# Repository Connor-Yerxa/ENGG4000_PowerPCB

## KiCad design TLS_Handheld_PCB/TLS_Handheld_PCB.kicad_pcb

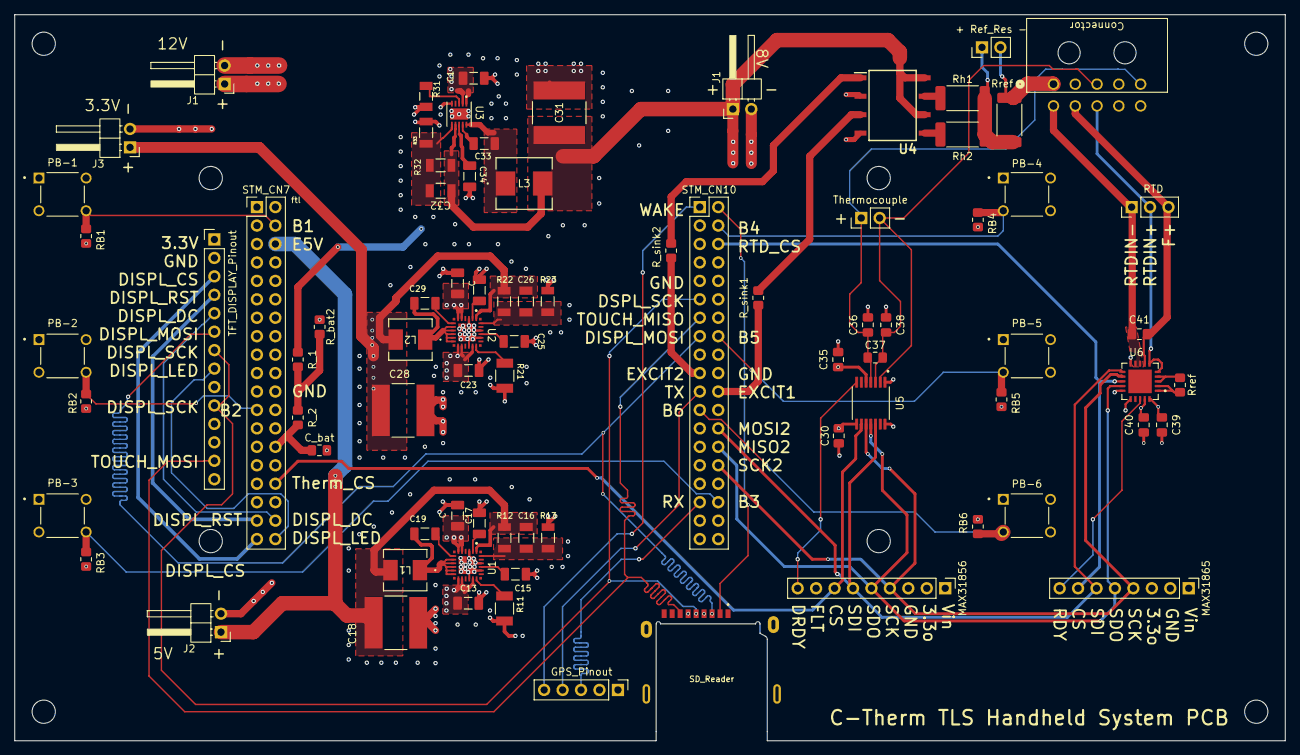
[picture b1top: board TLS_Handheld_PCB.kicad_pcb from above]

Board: 4 copper layers, 175.0 x 100.0 mm, 86 parts (0 on the bottom side), 63 nets.

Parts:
+ Ref_Res -: PinHeader_1x02_P2.54mm_Vertical
C, C13, C17, C23, C27, C34: 1uF; CAPC3216X180N
C1: 4.7uF; CAPC3216X180N
C15, C25: 1nF; CAPC3216X100N
C16, C26, C32: 10pF; CAP_C1206C-X7R-EB_KEM
C18, C28, C31: 100uF; CAP_NTJ_76B_9.5T_NIP
C19, C29, C33: 0.1uF; CAPC3216X100N
C30, C35, C37: 0.1uF; C_0805_2012Metric_Pad1.18x1.45mm_HandSolder
C36, C38, C39, C40, C41: 0.01uF; C_0805_2012Metric_Pad1.18x1.45mm_HandSolder
C#2: 1uF; CAPC3216X180N
C_bat: 0.1uF; C_0805_2012Metric_Pad1.18x1.45mm_HandSolder
Connector: 0430451000
GPS_Pinout: PinHeader_1x05_P2.54mm_Vertical
J1, J1#2, J2, J3: Conn_01x02_Pin; PinHeader_1x02_P2.54mm_Horizontal
L1, L2: 3.3uH; IND_IHLP-2020CZ
L3: 10uH; IND_ASPI-0630LR_ABR
MAX31856: PinHeader_1x09_P2.54mm_Vertical
MAX31865: PinHeader_1x08_P2.54mm_Vertical
PB-1, PB-2, PB-3, PB-4, PB-5, PB-6: SW_1825967-2
R11, R21: 41.2k; RES_ERJ14NF4122U
R12: 1M; RESC3116X65N
R13: 243k; RESC3116X60N
R22: 240k; RESC3116X60N
R23: 100k; RESC3116X65N
R31: 60.4k; RESC3116X65N
R32: 1.05M; RESC3116X60N
R33: 117k; RESC3216X70N
RB1, RB2, RB3, RB4, RB5, RB6: R_0805_2012Metric_Pad1.20x1.40mm_HandSolder
RTD: PinHeader_1x03_P2.54mm_Vertical
R_1, R_2: R_0805_2012Metric_Pad1.20x1.40mm_HandSolder
R_bat2: R_0805_2012Metric_Pad1.20x1.40mm_HandSolder
R_sink1, R_sink2: R_0805_2012Metric_Pad1.20x1.40mm_HandSolder
Rh1, Rh2: R_2512_6332Metric_Pad1.40x3.35mm_HandSolder
Rref: R_2512_6332Metric_Pad1.40x3.35mm_HandSolder
Rref#2: 4kohm; R_0805_2012Metric_Pad1.20x1.40mm_HandSolder
SD_Reader: CUI_MSD-3-A
STM_CN7, STM_CN10: PinHeader_2x19_P2.54mm_Vertical
TFT_DISPLAY_Pinout: PinHeader_1x14_P2.54mm_Vertical
Thermocouple: PinHeader_1x02_P2.54mm_Vertical
U1, U2: LT8640SEV_PBF; CONV_LT8640SEV_PBF
U3: LT8619EDD-TRPBF; 05-08-1699_ADI
U4: LAA108STR
U5: SOP65P640X110-14N
U6: QFN65P500X500X80-21N_MAXRTD_Pinless
hole: MountingHole_3.2mm_M3
hole#2, hole#3, hole#4: MountingHole_3.2mm_M3

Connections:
/3.3V: C26.1, C28.1, C30.1, C35.2, C39.2, C40.1, GPS_Pinout.1, J3.1, L2.2, MAX31856.1, MAX31865.1, R22.1, RB1.1, RB2.1, RB3.1, RB4.1, RB5.1, RB6.1, SD_Reader.4, TFT_DISPLAY_Pinout.1, U2.1 (BIAS), U5.5, U5.8, U6.19, U6.20
/5V: C16.1, C18.1, J2.1, L1.2, R12.1, STM_CN7.6, U1.1 (BIAS)
/8V: C31.1, C32.1, J1.1, L3.2, R32.1, U3.7 (BIAS), U4.6, U4.8
/FB1: C16.2, R12.2, R13.1, U1.24 (FB)
/FB2: C26.2, R22.2, R23.1, U2.24 (FB)
/FB3: C32.2, R32.2, R33.1, U3.6 (FB)
/Pin: C.2, C1.1, C13.2, C23.2, C#2.2, J1#2.1, R_1.2, U1.5 (VIN), U1.6 (VIN__1), U1.13 (VIN__2), U1.14 (VIN__3), U1.17 (EN), U2.5 (VIN), U2.6 (VIN__1), U2.13 (VIN__2), U2.14 (VIN__3), U2.17 (EN), U3.1 (VIN), U3.2 (EN/UV)
/SW1: C19.1, L1.1, U1.8 (SW), U1.9 (SW__1), U1.10 (SW__2), U1.11 (SW__3), U1.12 (SW__4)
/SW2: C29.1, L2.1, U2.8 (SW), U2.9 (SW__1), U2.10 (SW__2), U2.11 (SW__3), U2.12 (SW__4)
/SW3: C33.1, L3.1, U3.10 (SW)
B1: PB-1.4, RB1.2, STM_CN7.4
B2: PB-2.4, RB2.2, STM_CN7.23
B3: PB-3.4, RB3.2, STM_CN10.34
B4: PB-4.3, RB4.2, STM_CN10.4
B5: PB-5.3, RB5.2, STM_CN10.16
B6: PB-6.3, RB6.2, STM_CN10.23
BIAS: Rref#2.2, U6.1, U6.2
DISPL_CS: STM_CN7.37, TFT_DISPLAY_Pinout.3
DISPL_DC: STM_CN7.36, TFT_DISPLAY_Pinout.5
DISPL_LED: STM_CN7.38, TFT_DISPLAY_Pinout.8
DISPL_MOSI: SD_Reader.3, STM_CN10.15, TFT_DISPLAY_Pinout.6
DISPL_RST: STM_CN7.35, TFT_DISPLAY_Pinout.4
DISPL_SCK: SD_Reader.5, STM_CN10.11, TFT_DISPLAY_Pinout.7, TFT_DISPLAY_Pinout.10
EXCIT1: R_sink1.1, STM_CN10.22
EXCIT2: R_sink2.1, STM_CN10.19
GND: C.1, C1.2, C13.1, C15.1, C17.1, C18.2, C23.1, C25.1, C27.1, C28.2, C30.2, C31.2, C34.1, C35.1, C36.1, C38.2, C39.1, C40.2, C#2.1, C_bat.1, Connector.2, Connector.9, GPS_Pinout.2, J1.2, J1#2.2, J2.2, J3.2, MAX31856.3, MAX31865.2, PB-1.2, PB-2.2, PB-3.2, PB-4.1, PB-5.1, PB-6.1, R11.2, R13.2, R21.2, R23.2, R31.2, R33.2, R_bat2.2, SD_Reader.6, SD_Reader.G1, SD_Reader.G2, SD_Reader.G3, SD_Reader.G4, STM_CN7.22, STM_CN10.9, STM_CN10.20, TFT_DISPLAY_Pinout.2, U1.3 (GND), U1.16 (GND__1), U1.20 (SYNC/MODE), U1.22 (GND__2), U1.25 (GND__3), U1.26 (GND__4), U1.27 (GND__5), U1.28 (GND__6), U2.3 (GND), U2.16 (GND__1), U2.20 (SYNC/MODE), U2.22 (GND__2), U2.25 (GND__3), U2.26 (GND__4), U2.27 (GND__5), U2.28 (GND__6), U3.5 (SYNC), U3.11 (GND), U4.2, U4.4, U5.1, U5.14, U6.10, U6.15, U6.16
Heater+: + Ref_Res -.2, Connector.1, Rref.2
HeaterPre: + Ref_Res -.1, Rh1.2, Rh2.2, Rref.1
ISENSOR: Rref#2.1, U6.3, U6.4
MAX_SCK: MAX31856.4, MAX31865.4, STM_CN10.30, U5.10, U6.12
MAX_SDI: MAX31856.6, MAX31865.6, STM_CN10.26, U5.12, U6.11
MAX_SDO: MAX31856.5, MAX31865.5, STM_CN10.28, U5.11, U6.14
unnamed: C19.2, U1.7 (BST)
unnamed: C17.2, U1.2 (INTVCC)
unnamed: R11.1, U1.18 (RT)
unnamed: C15.2, U1.21 (TR/SS)
unnamed: C29.2, U2.7 (BST)
unnamed: C27.2, U2.2 (INTVCC)
unnamed: R21.1, U2.18 (RT)
unnamed: C25.2, U2.21 (TR/SS)
unnamed: C33.2, U3.9 (BST)
unnamed: C34.2, U3.8 (INTVCC)
unnamed: R31.1, U3.3 (RT)
RTD+: C41.1, Connector.7, RTD.3, U6.7
RTD-: C41.2, Connector.6, RTD.1, U6.8, U6.9
RTDDRDY: MAX31865.8, U6.18
RTDSens: Connector.8, RTD.2, U6.5, U6.6
RTD_CS: MAX31865.7, STM_CN10.6, U6.13
RX: GPS_Pinout.3, STM_CN10.33
SD_CS: SD_Reader.2, STM_CN10.2
SSRout-1: Rh1.1, U4.7
SSRout-2: Rh2.1, U4.5
SW1: R_sink2.2, U4.1
SW2: R_sink1.2, U4.3
TOUCH_MISO: SD_Reader.7, STM_CN10.13, TFT_DISPLAY_Pinout.13
TX: GPS_Pinout.4, STM_CN10.21
Therm_CS: MAX31856.7, STM_CN7.32, U5.9
Thermocouple+: C36.e, C37.2, Connector.5, Thermocouple.1, U5.4
Thermocouple-: C37.1, C38.1, Connector.3, Thermocouple.2, U5.2, U5.3
V_bat_node: R_1.1, R_2.2, R_bat2.1
Vbat_sense: C_bat.2, R_2.1, STM_CN7.28
WAKE: GPS_Pinout.5, STM_CN10.1
thermDRDY: MAX31856.9, U5.7

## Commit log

2026-01-23 Moved exciter closer to TLS Connector
2026-01-25 Add Marc's changes from From Jan 25.
2026-01-26 Rearrange components. The commint also adds the hardware the for the RTD and thermocouple module, silkscreen tags, and a bunch of wiring.
2026-01-26 Minor teaks.
2026-01-26 begin merging Power PCB and IO PCB. This commit has the updates trace widths, new nets to the STm headers, buttons with resistors, and screen header. Stuff to do: finish wiring the spi conneection fr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
2026-01-26 Complete wiring for screen SPI.
2026-01-26 Add a bunch of silkscreening.
2026-01-27 Add all components. Also did some lengthening of traces for matching parallel communication. Left to do is addinghole for screen and making sure there is enough clearance for all modules and componen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
2026-01-27 resize button spacing for screen and moved screen headers to center.
2026-01-27 Move GPS headers
2026-01-27 Add outlines for external MAX modules
2026-01-28 Flip Maxx modules so they can be mounted upsidown on the bottom of the board. I also made some changes to silk screens and vias to remove a bunch of wranings.
2026-01-28 Add Marc's changes the connect components to ground.
2026-01-28 Change trace thickness to comply with tolerances.
    Some of the ics might not work.
2026-01-28 Change clearance to better match PCBway.
2026-01-28 Undo clearance change.
2026-01-28 start work on clearance fixes.
    modified 8V regulator footprint, added not MAX rtd module not connected.
2026-01-28 Fully integrate new Max RTD module.
2026-01-28 Add holes for screen.
    Moved traces and a couple comonents to accomodate.
2026-01-28 Connect Max modules to STM header.
    Also added so extra silkscreening.
2026-01-28 Add header for measuring exciter current.
2026-01-28 Add label silkscreen
2026-01-28 stuff
2026-01-28 Add gerber files and missing silkscreen.
2026-01-29 Add pdf outputs.
2026-02-02 Minor Traces changes
2026-02-02 Create designator for relay and max ICs.
2026-02-02 Fix Wiring of thermocouple module and trace widths
2026-02-02 Remove thermocouple resistors. Not need only good for overvoltage protection above 40 V.
2026-02-02 Connect drdy pins of max module to headers.
2026-02-03 Space out vias for non power planes and thicken power header traces.
2026-02-03 New Gerbers
2026-02-03 Add marc's changes to the power reg ccts.
2026-02-03 Rename kicad project to TLS_Handheld_PCB
2026-02-03 Remove this pcb strip from sd card
2026-02-03 Fix Clearance issues with sd card
2026-02-04 Update gerber files.
2026-02-05 Add marc's changes f=to improve noise of 8 V regulator.
2026-02-05 Add Marc's minor changes to routing and vias.
2026-02-05 Fill in a couple plains.
2026-02-05 Added battery status circuity
2026-02-05 maybe duplicated work idk
2026-02-05 some final changes
2026-02-06 Add Marcs changes to inductors and traces widths.
2026-02-06 move power plnes in to fit edgecuts and new gerbers
2026-02-17 Add all components to folder for adding 3d models.
    Added links for 3D models to parts for me, Connor.
2026-03-26 Update relay switching.
2026-04-01 update rtd module wiring.
